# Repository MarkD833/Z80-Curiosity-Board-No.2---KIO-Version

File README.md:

# Zilog Z80 Curiosity Board #2 - The KIO Version

After my attempt to build a Z80 board met with reasonable success, I set my sights on a possible RetroDuino-Z80 board. This design is the pathfinder project with that goal in mind.

I wanted to have serial, parallel I/O and timer capability but aware of the space limitations, I decided to investigate the use of the Zilog Z80 KIO chip, or Z84C90 KIO as it's called.

This is a beast of a chip. It comes in a PLCC84 package which requires a big chunk of board space. The KIO combines the PIO, SIO  and CTC chips into one package.

The design still makes use of the PLCC44 Z80 CPU that I used previously.

## Description

The aim of this project is to provide the groundwork for a possible RetroDuino-Z80 board along the lines of my [RetroDuino-8085](https://github.com/MarkD833/RetroDuino-8085) board.

I'm hoping that this design can also run CP/M and I will be using Grant Searles excellent [web page](http://searle.x10host.com/cpm/index.html) as my starting point.

## Design

The design is fairly straightforward, using a 128Kb SRAM from my stash as well as a 64Kb EEPROM for non volatile storage. Only the lower 64Kb of SRAM is currently accessible.

I studied other designs that I came across and liked a concept that I came across whereby on startup, the whole of the ROM was copied into RAM and then the ROM disabled. The hardware was configured so that the ROM and the RAM both occupied the same 64Kb, but initially any read accessed would go to the ROM and any write accesses would go to the RAM. Once the ROM was copied into RAM (at the same addresses), the ROM would be disabled giving full read/write access to the RAM and the Z80 would continue to execute instructions as if nothing had happened.

The design uses simple logic chips to handle the address decoding, as well as the disabling of the ROM etc.

# The board layout

This is an annotated 3D view of the board generated by Kicad as it stands at v1.0.

# Software

I adapted Dave Dunfields MONZ80 monitor program to work with this board. MONZ80 can be found on [Dave's website](https://dunfield.themindfactory.com/dnldsrc.htm) as part of the MONITORS.ZIP file. There is no documentation for the monitor but most of the commands are self explanatory.

The monitor code needs a slight tweek to reflect the address of the SIO registers within the KIO chip. My modified version of MONZ80 is in the code folder and has been edited to allow assembly using the free online assembler at [ASM80.COM](https://asm80.com) - select the Z80 CPU.

The code folder includes the assembler files to run CP/M from [Grant Searles web site](http://searle.x10host.com/cpm/index.html) but configured to assemble using the ASM80 online assembler. I've also included my instructions for loading CP/M onto the board, which are almost identical to Grants instructions.

# Known errors

* Nothing so far. 

# Conclusions

The board works as I had hoped it would. I need to develop routines for software SPI and also software I2C.

## License

This project is licensed under the GNU General Public License v3.0 - see the LICENSE.md file for details

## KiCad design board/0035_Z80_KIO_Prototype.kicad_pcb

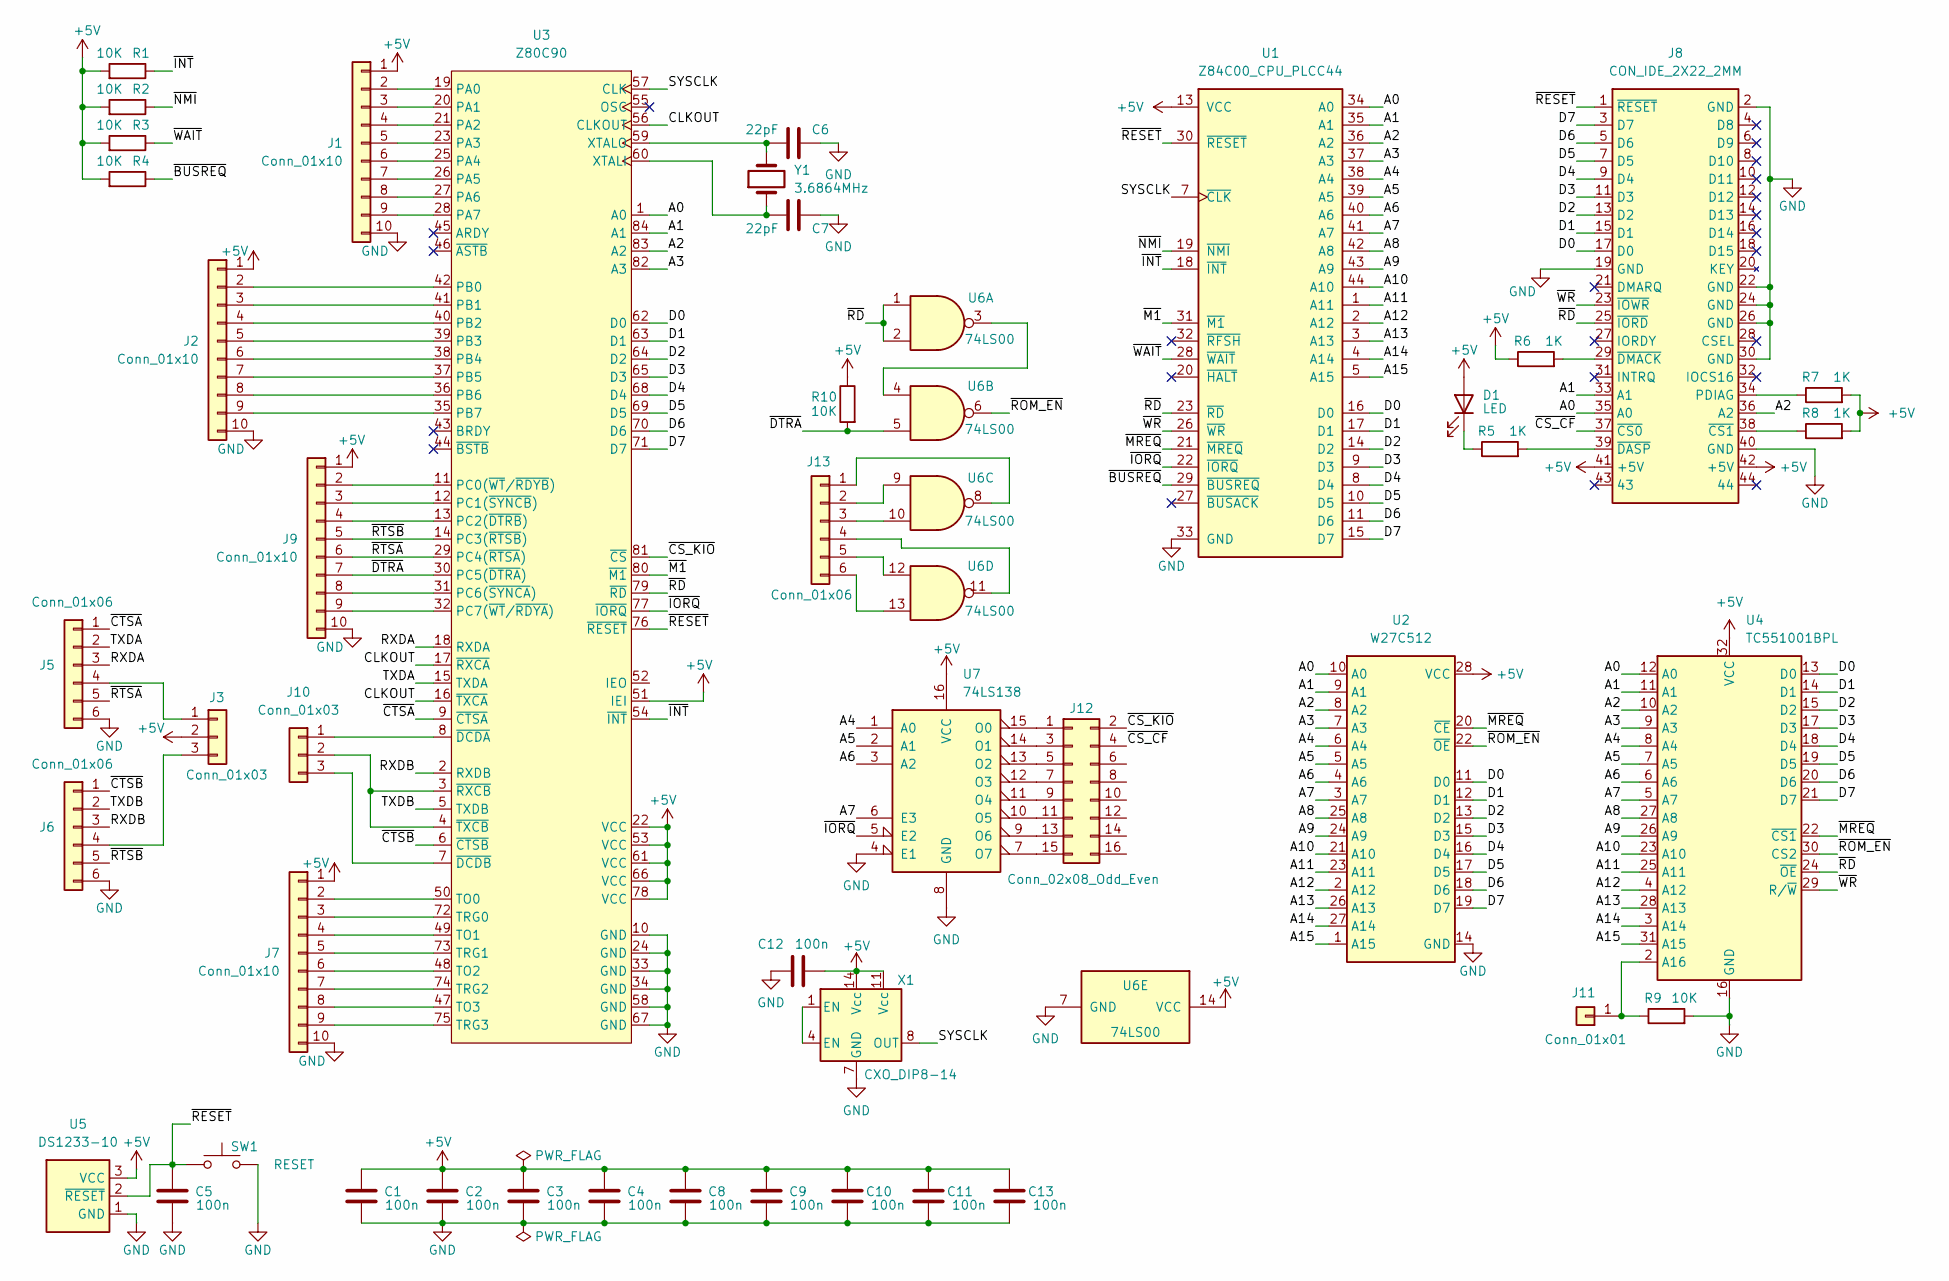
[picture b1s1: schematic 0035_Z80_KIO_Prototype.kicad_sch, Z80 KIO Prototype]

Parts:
C1, C2, C3, C4, C5, C8, C9, C10, C11, C12, C13: 100n; C_0805_2012Metric_Pad1.18x1.45mm_HandSolder
C6, C7: 22pF; C_0805_2012Metric_Pad1.18x1.45mm_HandSolder
D1: LED; LED_0805_2012Metric_Pad1.15x1.40mm_HandSolder
J1, J2, J7, J9: Conn_01x10; PinHeader_1x10_P2.54mm_Vertical
J3: Conn_01x03; PinSocket_1x03_P2.54mm_Vertical
J5, J6, J13: Conn_01x06; PinHeader_1x06_P2.54mm_Vertical
J8: CON_IDE_2X22_2MM; CompactFlashHeader_2x22_P2.00mm_Vertical
J10: Conn_01x03; PinHeader_1x03_P2.54mm_Vertical
J11: Conn_01x01; PinHeader_1x01_P2.54mm_Vertical
J12: Conn_02x08_Odd_Even; PinHeader_2x08_P2.54mm_Vertical
R1, R2, R3, R4, R9, R10: 10K; R_0805_2012Metric_Pad1.20x1.40mm_HandSolder
R5, R6, R7, R8: 1K; R_0805_2012Metric_Pad1.20x1.40mm_HandSolder
SW1: RESET; SW_TH_Tactile
U1: Z84C00_CPU_PLCC44; PLCC-44_THT-Socket
U2: W27C512; DIP-28_W15.24mm
U3: Z80C90; PLCC-84_THT-Socket
U4: TC551001BPL; DIP-32_W15.24mm_Socket
U5: DS1233-10; TO-92L_Inline
U6: 74LS00; DIP-14_W7.62mm_Socket
U7: 74LS138; DIP-16_W7.62mm_Socket
X1: CXO_DIP8-14; DIP-14_W7.62mm-XTAL_SOCKET
Y1: 3.6864MHz; Crystal_HC49-U_Vertical

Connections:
+5V: C1.2, C2.2, C3.2, C4.2, C8.2, C9.2, C10.2, C11.2, C12.2, C13.2, D1.2 (A), J1.1, J2.1, J3.2, J7.1, J8.41 (+5V), J8.42 (+5V), J9.1, R1.2, R2.2, R3.2, R4.2, R6.1, R7.2, R8.2, R10.1, U1.13 (VCC), U2.28 (VCC), U3.22 (VCC), U3.51 (IEI), U3.53 (VCC), U3.61 (VCC), U3.66 (VCC), U3.78 (VCC), U4.32 (VCC), U5.3 (VCC), U6.14 (VCC), U7.16 (VCC), X1.11 (Vcc), X1.14 (Vcc)
/A0: J8.35 (A0), U1.34 (A0), U2.10 (A0), U3.1 (A0), U4.12 (A0)
/A1: J8.33 (A1), U1.35 (A1), U2.9 (A1), U3.84 (A1), U4.11 (A1)
/A2: J8.36 (A2), U1.36 (A2), U2.8 (A2), U3.83 (A2), U4.10 (A2)
/A3: U1.37 (A3), U2.7 (A3), U3.82 (A3), U4.9 (A3)
/A4: U1.38 (A4), U2.6 (A4), U4.8 (A4), U7.1 (A0)
/A5: U1.39 (A5), U2.5 (A5), U4.7 (A5), U7.2 (A1)
/A6: U1.40 (A6), U2.4 (A6), U4.6 (A6), U7.3 (A2)
/A7: U1.41 (A7), U2.3 (A7), U4.5 (A7), U7.6 (E3)
/A8: U1.42 (A8), U2.25 (A8), U4.27 (A8)
/A9: U1.43 (A9), U2.24 (A9), U4.26 (A9)
/A10: U1.44 (A10), U2.21 (A10), U4.23 (A10)
/A11: U1.1 (A11), U2.23 (A11), U4.25 (A11)
/A12: U1.2 (A12), U2.2 (A12), U4.4 (A12)
/A13: U1.3 (A13), U2.26 (A13), U4.28 (A13)
/A14: U1.4 (A14), U2.27 (A14), U4.3 (A14)
/A15: U1.5 (A15), U2.1 (A15), U4.31 (A15)
/CLKOUT: U3.16 (~TXCA), U3.17 (~RXCA), U3.56 (CLKOUT)
/D0: J8.17 (D0), U1.16 (D0), U2.11 (D0), U3.62 (D0), U4.13 (D0)
/D1: J8.15 (D1), U1.17 (D1), U2.12 (D1), U3.63 (D1), U4.14 (D1)
/D2: J8.13 (D2), U1.14 (D2), U2.13 (D2), U3.64 (D2), U4.15 (D2)
/D3: J8.11 (D3), U1.9 (D3), U2.15 (D3), U3.65 (D3), U4.17 (D3)
/D4: J8.9 (D4), U1.8 (D4), U2.16 (D4), U3.68 (D4), U4.18 (D4)
/D5: J8.7 (D5), U1.10 (D5), U2.17 (D5), U3.69 (D5), U4.19 (D5)
/D6: J8.5 (D6), U1.11 (D6), U2.18 (D6), U3.70 (D6), U4.20 (D6)
/D7: J8.3 (D7), U1.15 (D7), U2.19 (D7), U3.71 (D7), U4.21 (D7)
/RXDA: J5.3, U3.18 (RXDA)
/RXDB: J6.3, U3.2 (RXDB)
/SYSCLK: U1.7 (~CLK), U3.57 (CLK), X1.8 (OUT)
/TXDA: J5.2, U3.15 (TXDA)
/TXDB: J6.2, U3.5 (TXDB)
/~BUSREQ: R4.1, U1.29 (~BUSREQ)
/~CS_CF: J8.37 (~CS0), J12.4
/~CS_KIO: J12.2, U3.81 (~CS)
/~CTSA: J5.1, U3.9 (~CTSA)
/~CTSB: J6.1, U3.6 (~CTSB)
/~DTRA: J9.7, R10.2, U3.30 (PC5(~DTRA)), U6.5
/~INT: R1.1, U1.18 (~INT), U3.54 (~INT)
/~IORQ: U1.22 (~IORQ), U3.77 (~IORQ), U7.5 (E2)
/~M1: U1.31 (~M1), U3.80 (~M1)
/~MREQ: U1.21 (~MREQ), U2.20 (~CE), U4.22 (~CS1)
/~NMI: R2.1, U1.19 (~NMI)
/~RD: J8.25 (~IORD), U1.23 (~RD), U3.79 (~RD), U4.24 (~OE), U6.1, U6.2
/~RESET: C5.2, J8.1 (~RESET), SW1.1, U1.30 (~RESET), U3.76 (~RESET), U5.2 (~RESET)
/~ROM_EN: U2.22 (~OE), U4.30 (CS2), U6.6
/~RTSA: J5.5, J9.6, U3.29 (PC4(~RTSA))
/~RTSB: J6.5, J9.5, U3.14 (PC3(~RTSB))
/~WAIT: R3.1, U1.28 (~WAIT)
/~WR: J8.23 (~IOWR), U1.26 (~WR), U4.29 (R/~W)
GND: C1.1, C2.1, C3.1, C4.1, C5.1, C6.2, C7.1, C8.1, C9.1, C10.1, C11.1, C12.1, C13.1, J1.10, J2.10, J5.6, J6.6, J7.10, J8.2 (GND), J8.19 (GND), J8.22 (GND), J8.24 (GND), J8.26 (GND), J8.30 (GND), J8.40 (GND), J9.10, R9.2, SW1.2, U1.33 (GND), U2.14 (GND), U3.10 (GND), U3.24 (GND), U3.33 (GND), U3.34 (GND), U3.58 (GND), U3.67 (GND), U4.16 (GND), U5.1 (GND), U6.7 (GND), U7.4 (E1), U7.8 (GND), X1.7 (GND)
unnamed: D1.1 (K), R5.1
unnamed: J1.2, U3.19 (PA0)
unnamed: J1.3, U3.20 (PA1)
unnamed: J1.4, U3.21 (PA2)
unnamed: J1.5, U3.23 (PA3)
unnamed: J1.6, U3.25 (PA4)
unnamed: J1.7, U3.26 (PA5)
unnamed: J1.8, U3.27 (PA6)
unnamed: J1.9, U3.28 (PA7)
unnamed: J2.2, U3.42 (PB0)
unnamed: J2.3, U3.41 (PB1)
unnamed: J2.4, U3.40 (PB2)
unnamed: J2.5, U3.39 (PB3)
unnamed: J2.6, U3.38 (PB4)
unnamed: J2.7, U3.37 (PB5)
unnamed: J2.8, U3.36 (PB6)
unnamed: J2.9, U3.35 (PB7)
unnamed: J3.1, J5.4
unnamed: J3.3, J6.4
unnamed: J7.2, U3.50 (TO0)
unnamed: J7.3, U3.72 (TRG0)
unnamed: J7.4, U3.49 (TO1)
unnamed: J7.5, U3.73 (TRG1)
unnamed: J7.6, U3.48 (TO2)
unnamed: J7.7, U3.74 (TRG2)
unnamed: J7.8, U3.47 (TO3)
unnamed: J7.9, U3.75 (TRG3)
unnamed: J8.34 (PDIAG), R7.1
unnamed: J8.38 (~CS1), R8.1
unnamed: J8.39 (~DASP), R5.2
unnamed: J8.29 (~DMACK), R6.2
unnamed: J9.2, U3.11 (PC0(~WT/~RDYB))
unnamed: J9.3, U3.12 (PC1(~SYNCB))
unnamed: J9.4, U3.13 (PC2(~DTRB))
unnamed: J9.8, U3.31 (PC6(~SYNCA))
unnamed: J9.9, U3.32 (PC7(~WT/~RDYA))
unnamed: J10.1, U3.8 (~DCDA)
unnamed: J10.2, U3.3 (~RXCB), U3.4 (~TXCB)
unnamed: J10.3, U3.7 (~DCDB)
unnamed: J11.1, R9.1, U4.2 (A16)
unnamed: J12.1, U7.15 (O0)
unnamed: J12.3, U7.14 (O1)
unnamed: J12.5, U7.13 (O2)
unnamed: J12.7, U7.12 (O3)
unnamed: J12.9, U7.11 (O4)
unnamed: J12.11, U7.10 (O5)
unnamed: J12.13, U7.9 (O6)
unnamed: J12.15, U7.7 (O7)
unnamed: J13.1, U6.8
unnamed: J13.2, U6.9
unnamed: J13.3, U6.10
unnamed: J13.4, U6.11
unnamed: J13.5, U6.12
unnamed: J13.6, U6.13
unnamed: C7.2, U3.60 (XTALI), Y1.1
unnamed: C6.1, U3.59 (XTALO), Y1.2
unnamed: U6.3, U6.4
unnamed: X1.1 (EN), X1.4 (EN)

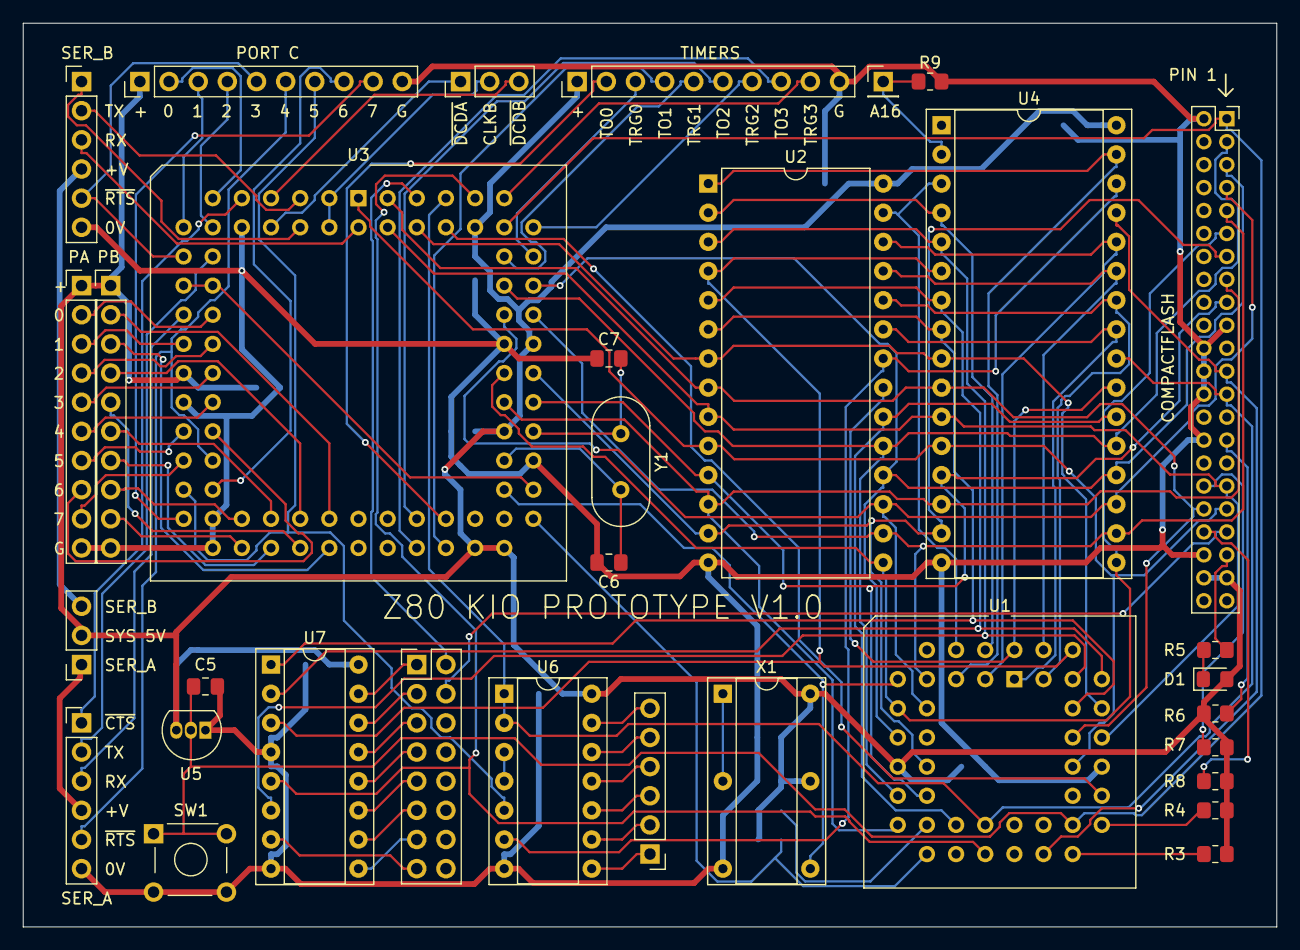
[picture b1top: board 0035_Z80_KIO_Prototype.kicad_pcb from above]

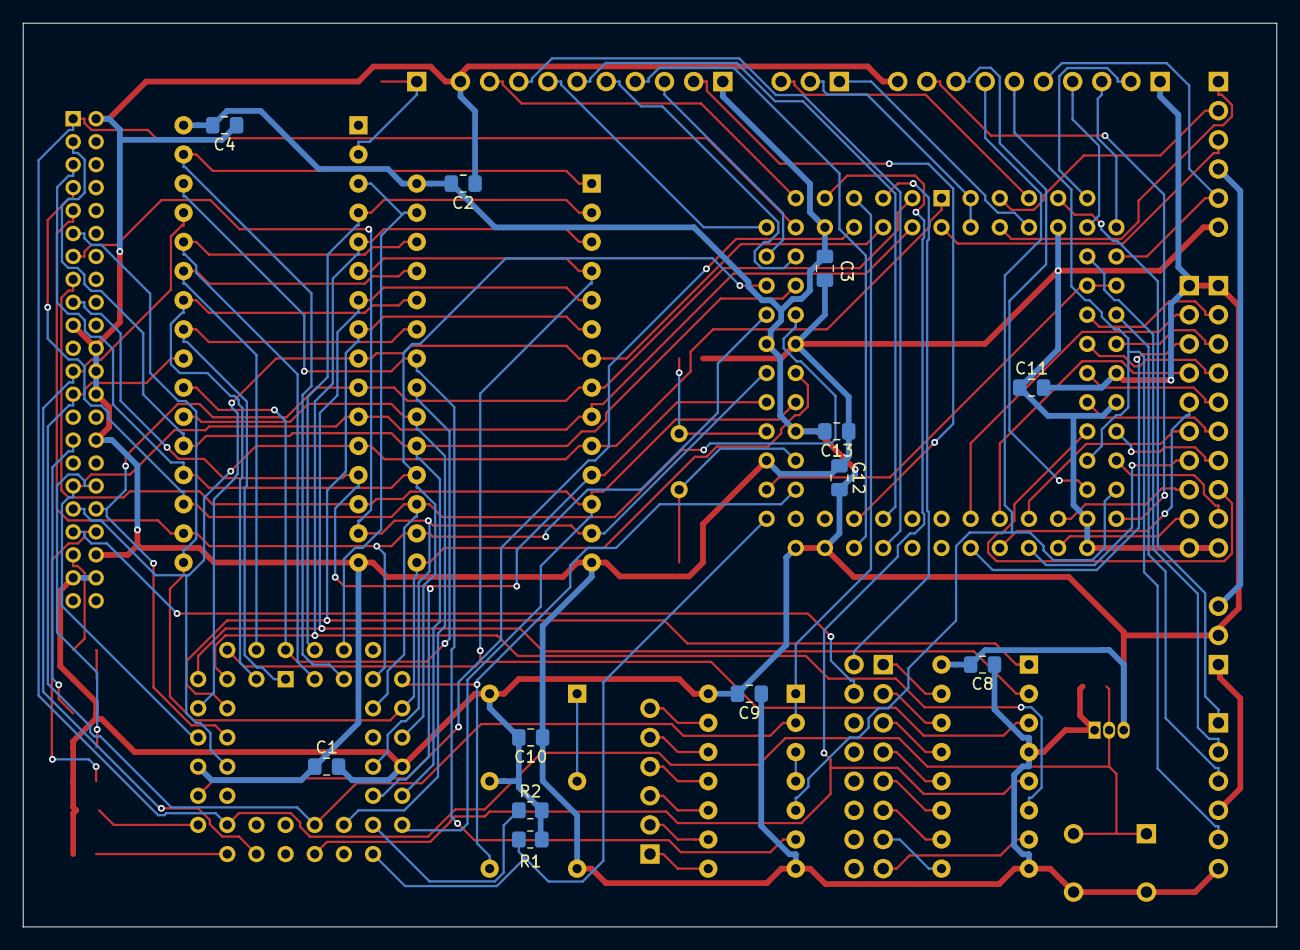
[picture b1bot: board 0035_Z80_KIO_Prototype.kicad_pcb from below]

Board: 2 copper layers, 109.2 x 78.7 mm, 45 parts (12 on the bottom side), 108 nets.

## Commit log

2024-08-19 added monitor and BASIC notes
2024-08-19 added code
2024-08-19 additional files
2024-08-19 added MBASIC package
